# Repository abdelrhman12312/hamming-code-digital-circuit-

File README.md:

# hamming-code-digital-circuit-
you can view the pcb here : https://kicanvas.org/?github=https%3A%2F%2Fgithub.com%2Fabdelrhman12312%2Fhamming-code-digital-circuit-%2Ftree%2Fmain%2Fhamming%2520code

In computer science and telecommunication, Hamming codes are a family of linear error-correcting codes. Hamming codes can detect one-bit and two-bit errors, or correct one-bit errors without detection of uncorrected errors. By contrast, the simple parity code cannot correct errors, and can detect only an odd number of bits in error. Hamming codes are perfect codes, that is, they achieve the highest possible rate for codes with their block length and minimum distance of three.[1] Richard W. Hamming invented Hamming codes in 1950 as a way of automatically correcting errors introduced by punched card readers. In his original paper, Hamming elaborated his general idea, but specifically focused on the Hamming(7,4) code which adds three parity bits to four bits of data.

## Description
If more error-correcting bits are included with a message, and if those bits can be arranged such that different incorrect bits produce different error results, then bad bits could be identified. In a seven-bit message, there are seven possible single bit errors, so three error control bits could potentially specify not only that an error occurred but also which bit caused the error.

Hamming studied the existing coding schemes, including two-of-five, and generalized their concepts. To start with, he developed a nomenclature to describe the system, including the number of data bits and error-correction bits in a block. For instance, parity includes a single bit for any data word, so assuming ASCII words with seven bits, Hamming described this as an (8,7) code, with eight bits in total, of which seven are data. The repetition example would be (3,1), following the same logic. The code rate is the second number divided by the first, for our repetition example, 1/3.

Hamming also noticed the problems with flipping two or more bits, and described this as the "distance" (it is now called the Hamming distance, after him). Parity has a distance of 2, so one bit flip can be detected but not corrected, and any two bit flips will be invisible. The (3,1) repetition has a distance of 3, as three bits need to be flipped in the same triple to obtain another code word with no visible errors. It can correct one-bit errors or it can detect - but not correct - two-bit errors. A (4,1) repetition (each bit is repeated four times) has a distance of 4, so flipping three bits can be detected, but not corrected. When three bits flip in the same group there can be situations where attempting to correct will produce the wrong code word. In general, a code with distance k can detect but not correct k − 1 errors.

Hamming was interested in two problems at once: increasing the distance as much as possible, while at the same time increasing the code rate as much as possible. During the 1940s he developed several encoding schemes that were dramatic improvements on existing codes. The key to all of his systems was to have the parity bits overlap, such that they managed to check each other as well as the data.

## General algorithm
The following general algorithm generates a single-error correcting (SEC) code for any number of bits. The main idea is to choose the error-correcting bits such that the index-XOR (the XOR of all the bit positions containing a 1) is 0. We use positions 1, 10, 100, etc. (in binary) as the error-correcting bits, which guarantees it is possible to set the error-correcting bits so that the index-XOR of the whole message is 0. If the receiver receives a string with index-XOR 0, they can conclude there were no corruptions, and otherwise, the index-XOR indicates the index of the corrupted bit.

An algorithm can be deduced from the following description:

Number the bits starting from 1: bit 1, 2, 3, 4, 5, 6, 7, etc.
Write the bit numbers in binary: 1, 10, 11, 100, 101, 110, 111, etc.
All bit positions that are powers of two (have a single 1 bit in the binary form of their position) are parity bits: 1, 2, 4, 8, etc. (1, 10, 100, 1000)
All other bit positions, with two or more 1 bits in the binary form of their position, are data bits.
Each data bit is included in a unique set of 2 or more parity bits, as determined by the binary form of its bit position.
Parity bit 1 covers all bit positions which have the least significant bit set: bit 1 (the parity bit itself), 3, 5, 7, 9, etc.
Parity bit 2 covers all bit positions which have the second least significant bit set: bits 2-3, 6-7, 10-11, etc.
Parity bit 4 covers all bit positions which have the third least significant bit set: bits 4–7, 12–15, 20–23, etc.
Parity bit 8 covers all bit positions which have the fourth least significant bit set: bits 8–15, 24–31, 40–47, etc.
In general each parity bit covers all bits where the bitwise AND of the parity position and the bit position is non-zero.
If a byte of data to be encoded is 10011010, then the data word (using _ to represent the parity bits) would be __1_001_1010, and the code word is 011100101010.

The choice of the parity, even or odd, is irrelevant but the same choice must be used for both encoding and decoding.

This general rule can be shown visually:

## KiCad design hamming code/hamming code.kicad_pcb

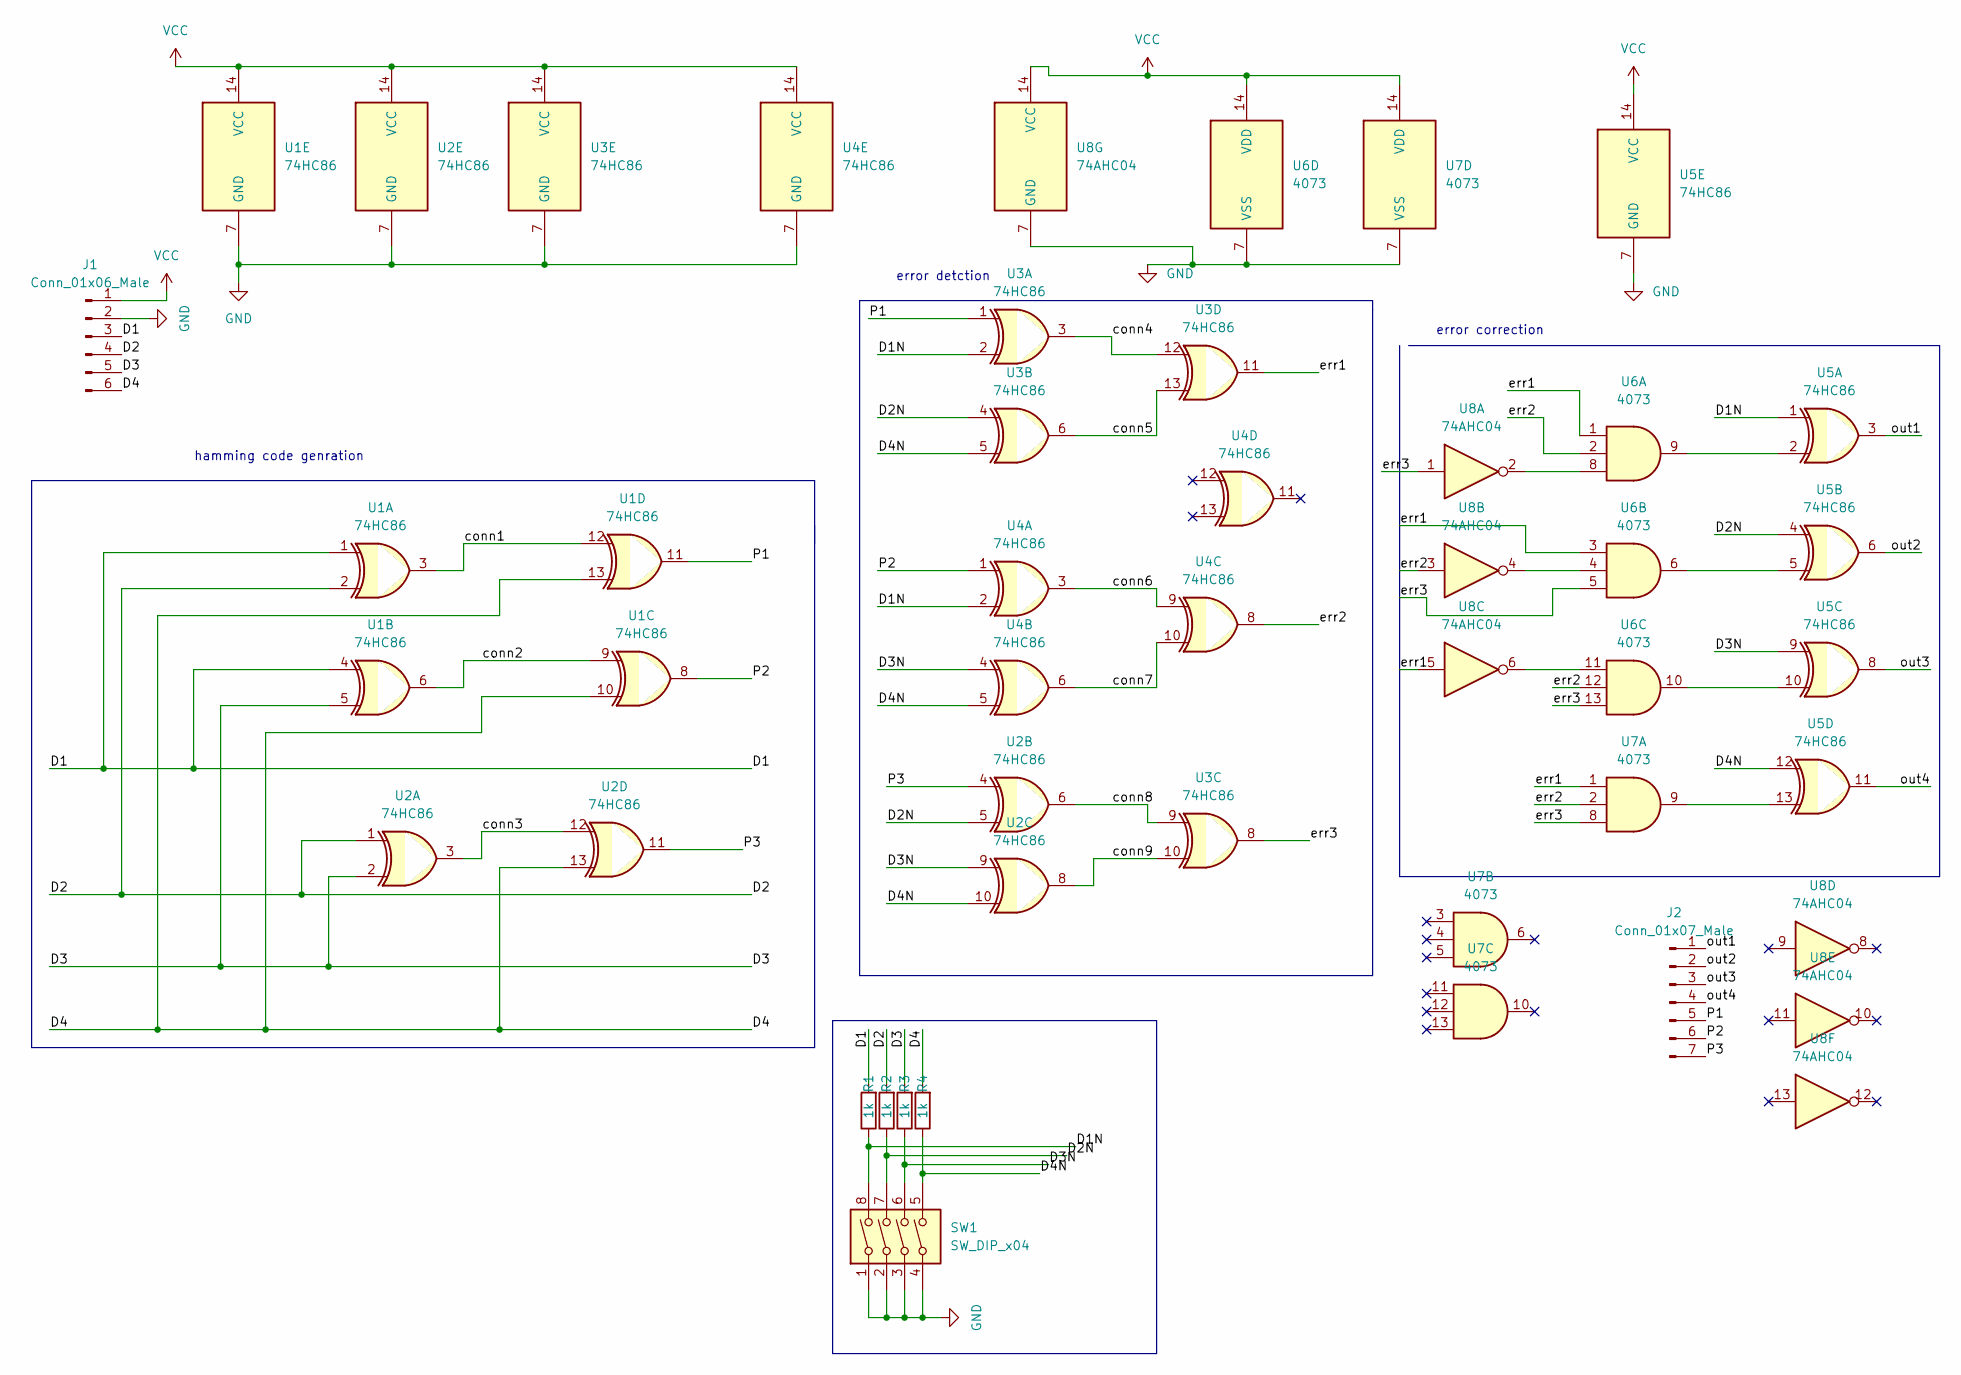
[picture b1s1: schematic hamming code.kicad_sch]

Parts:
J1: Conn_01x06_Male; PinHeader_1x06_P2.54mm_Vertical
J2: Conn_01x07_Male; PinHeader_1x07_P2.54mm_Vertical
R1, R2, R3, R4: 1k; R_Axial_DIN0204_L3.6mm_D1.6mm_P5.08mm_Horizontal
SW1: SW_DIP_x04; SW_DIP_SPSTx04_Slide_6.7x11.72mm_W7.62mm_P2.54mm_LowProfile
U1, U2, U3, U4, U5: 74HC86; DIP-14_W7.62mm
U6, U7: 4073; DIP-14_W7.62mm
U8: 74AHC04; DIP-14_W7.62mm

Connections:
/D1: J1.3, R1.2, U1.1, U1.4
/D1N: R1.1, SW1.8, U3.2, U4.2, U5.1
/D2: J1.4, R2.2, U1.2, U2.1
/D2N: R2.1, SW1.7, U2.5, U3.4, U5.4
/D3: J1.5, R3.2, U1.5, U2.2
/D3N: R3.1, SW1.6, U2.9, U4.4, U5.9
/D4: J1.6, R4.2, U1.10, U1.13, U2.13
/D4N: R4.1, SW1.5, U2.10, U3.5, U4.5, U5.12
/P1: J2.5, U1.11, U3.1
/P2: J2.6, U1.8, U4.1
/P3: J2.7, U2.4, U2.11
/conn1: U1.3, U1.12
/conn2: U1.6, U1.9
/conn3: U2.3, U2.12
/conn4: U3.3, U3.12
/conn5: U3.6, U3.13
/conn6: U4.3, U4.9
/conn7: U4.6, U4.10
/conn8: U2.6, U3.9
/conn9: U2.8, U3.10
/err1: U3.11, U6.1, U6.3, U7.1, U8.5
/err2: U4.8, U6.2, U6.12, U7.2, U8.3
/err3: U3.8, U6.5, U6.13, U7.8, U8.1
/out1: J2.1, U5.3
/out2: J2.2, U5.6
/out3: J2.3, U5.8
/out4: J2.4, U5.11
GND: J1.2, SW1.1, SW1.2, SW1.3, SW1.4, U1.7 (GND), U2.7 (GND), U3.7 (GND), U4.7 (GND), U5.7 (GND), U6.7 (VSS), U7.7 (VSS), U8.7 (GND)
unnamed: U5.2, U6.9
unnamed: U5.5, U6.6
unnamed: U5.10, U6.10
unnamed: U5.13, U7.9
unnamed: U6.4, U8.4
unnamed: U6.8, U8.2
unnamed: U6.11, U8.6
VCC: J1.1, U1.14 (VCC), U2.14 (VCC), U3.14 (VCC), U4.14 (VCC), U5.14 (VCC), U6.14 (VDD), U7.14 (VDD), U8.14 (VCC)

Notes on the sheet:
error detction
hamming code genration
error correction

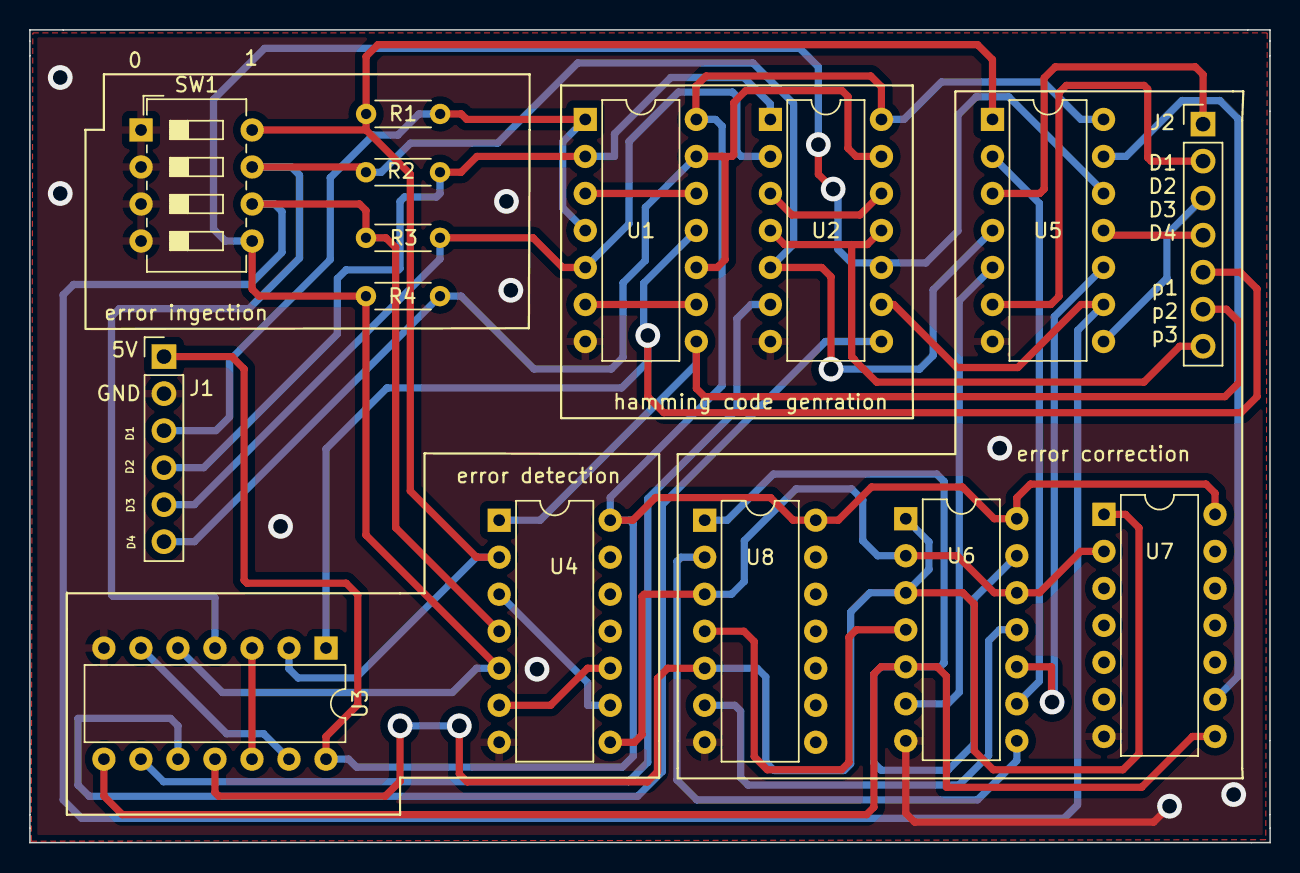
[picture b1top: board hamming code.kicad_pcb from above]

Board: 2 copper layers, 85.1 x 55.8 mm, 15 parts (0 on the bottom side), 36 nets.
